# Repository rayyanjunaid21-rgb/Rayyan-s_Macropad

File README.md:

# Rayyan-s_Macropad
Just a cool macropad
It has 6 keys and a rotary encoder, all connected to the Seeed Studio Xiao

## PCB
Here's a picture of my PCB and Schematics:

*Electrical schematic showing the key matrix, diodes, rotary encoder, and microcontroller*

*Custom PCB layout designed for a 2×3 key matrix with a rotary encoder and XIAO RP2040.*

## CAD
Here is the 3D printed Case

*Complete assembled macropad showing key layout and rotary encoder.*

## BOM
For this project, I would need:
- 6 Through-hole 1N4148 Diodes
- 6 MX-Style switches
- 1 EC11 Rotary encoder
- 6 Blank DSA keycaps
- 4 M3x16mm screws
- 4 M3x5mx4mm heatset inserts
- Soldering Iron

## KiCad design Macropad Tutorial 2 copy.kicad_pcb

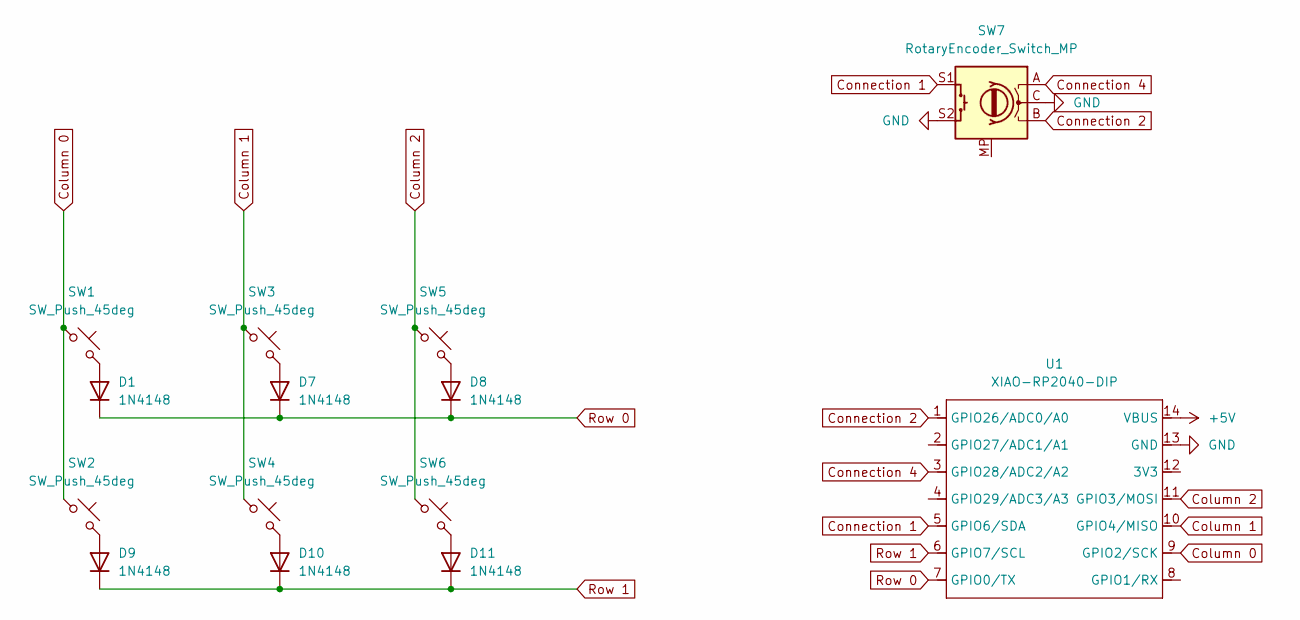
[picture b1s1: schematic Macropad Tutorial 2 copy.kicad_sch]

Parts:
D1, D7, D8, D9, D10, D11: 1N4148; D_DO-35_SOD27_P7.62mm_Horizontal
SW1, SW2, SW3, SW4, SW5, SW6: SW_Push_45deg; SW_Cherry_MX_1.00u_PCB
SW7: RotaryEncoder_Switch_MP; RotaryEncoder_Alps_EC11E-Switch_Vertical_H20mm
U1: XIAO-RP2040-DIP

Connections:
+5V: U1.14 (VBUS)
Column 0: SW1.1, SW2.1, U1.9 (GPIO2/SCK)
Column 1: SW3.1, SW4.1, U1.10 (GPIO4/MISO)
Column 2: SW5.1, SW6.1, U1.11 (GPIO3/MOSI)
Connection 1: SW7.S1, U1.5 (GPIO6/SDA)
Connection 2: SW7.B, U1.1 (GPIO26/ADC0/A0)
Connection 4: SW7.A, U1.3 (GPIO28/ADC2/A2)
GND: SW7.C, SW7.S2, U1.13 (GND)
unnamed: D1.2 (A), SW1.2
unnamed: D7.2 (A), SW3.2
unnamed: D8.2 (A), SW5.2
unnamed: D9.2 (A), SW2.2
unnamed: D10.2 (A), SW4.2
unnamed: D11.2 (A), SW6.2
Row 0: D1.1 (K), D7.1 (K), D8.1 (K), U1.7 (GPIO0/TX)
Row 1: D9.1 (K), D10.1 (K), D11.1 (K), U1.6 (GPIO7/SCL)

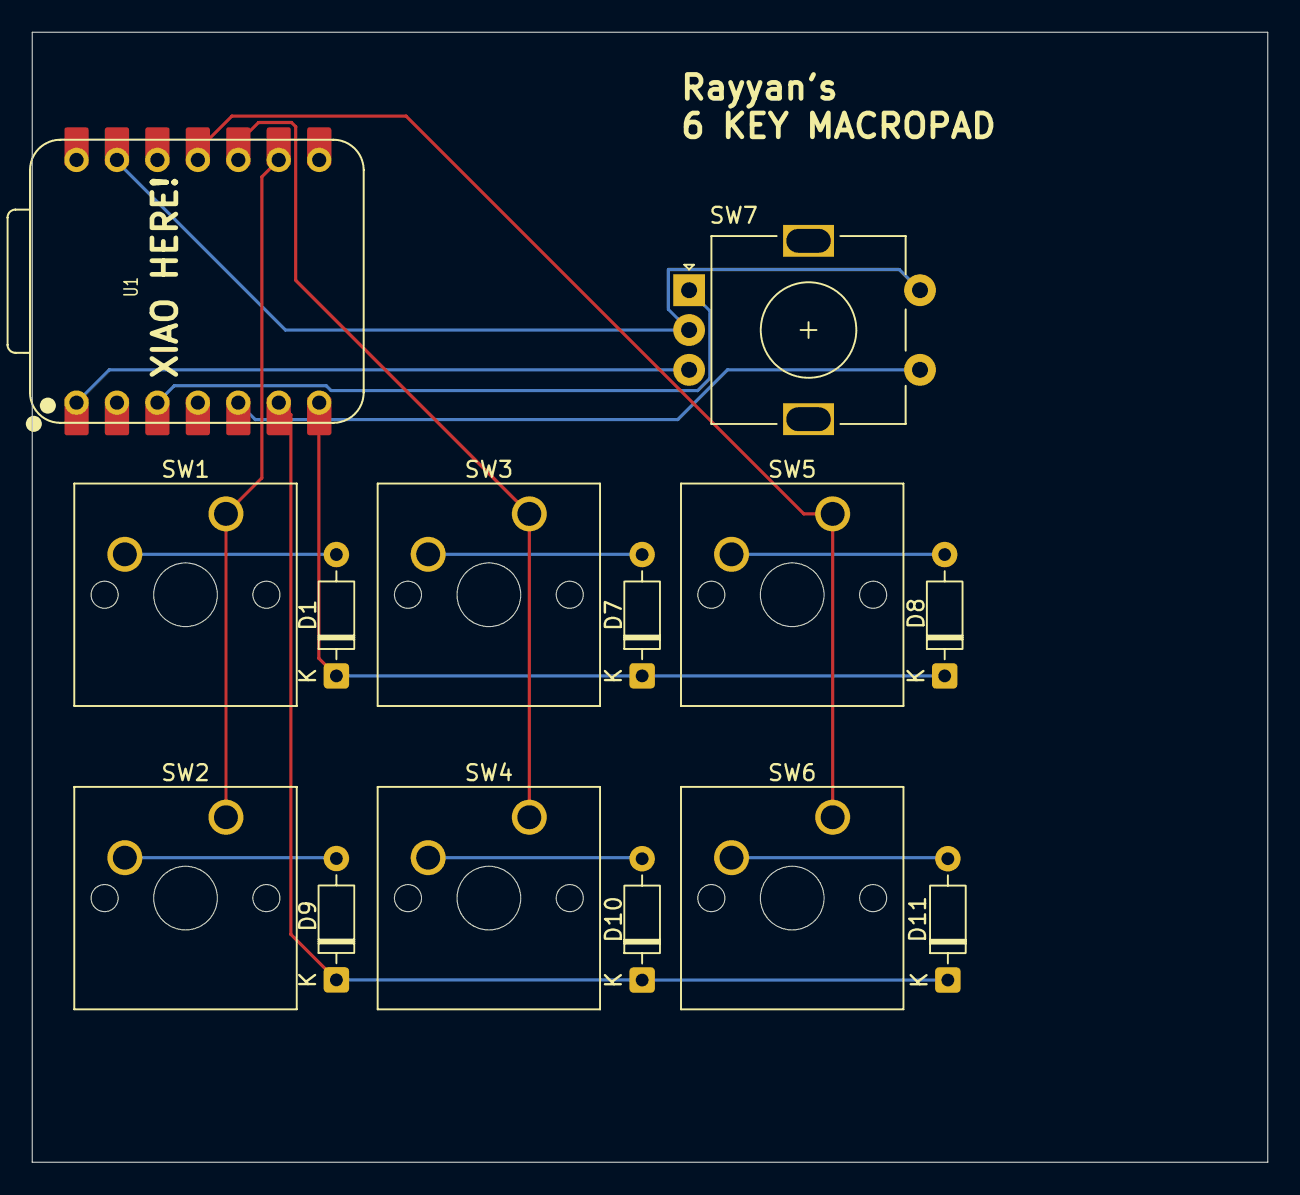
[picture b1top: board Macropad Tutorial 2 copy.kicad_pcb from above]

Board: 2 copper layers, 77.6 x 71.0 mm, 14 parts (0 on the bottom side), 15 nets.

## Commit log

2026-02-01 Create CAD
